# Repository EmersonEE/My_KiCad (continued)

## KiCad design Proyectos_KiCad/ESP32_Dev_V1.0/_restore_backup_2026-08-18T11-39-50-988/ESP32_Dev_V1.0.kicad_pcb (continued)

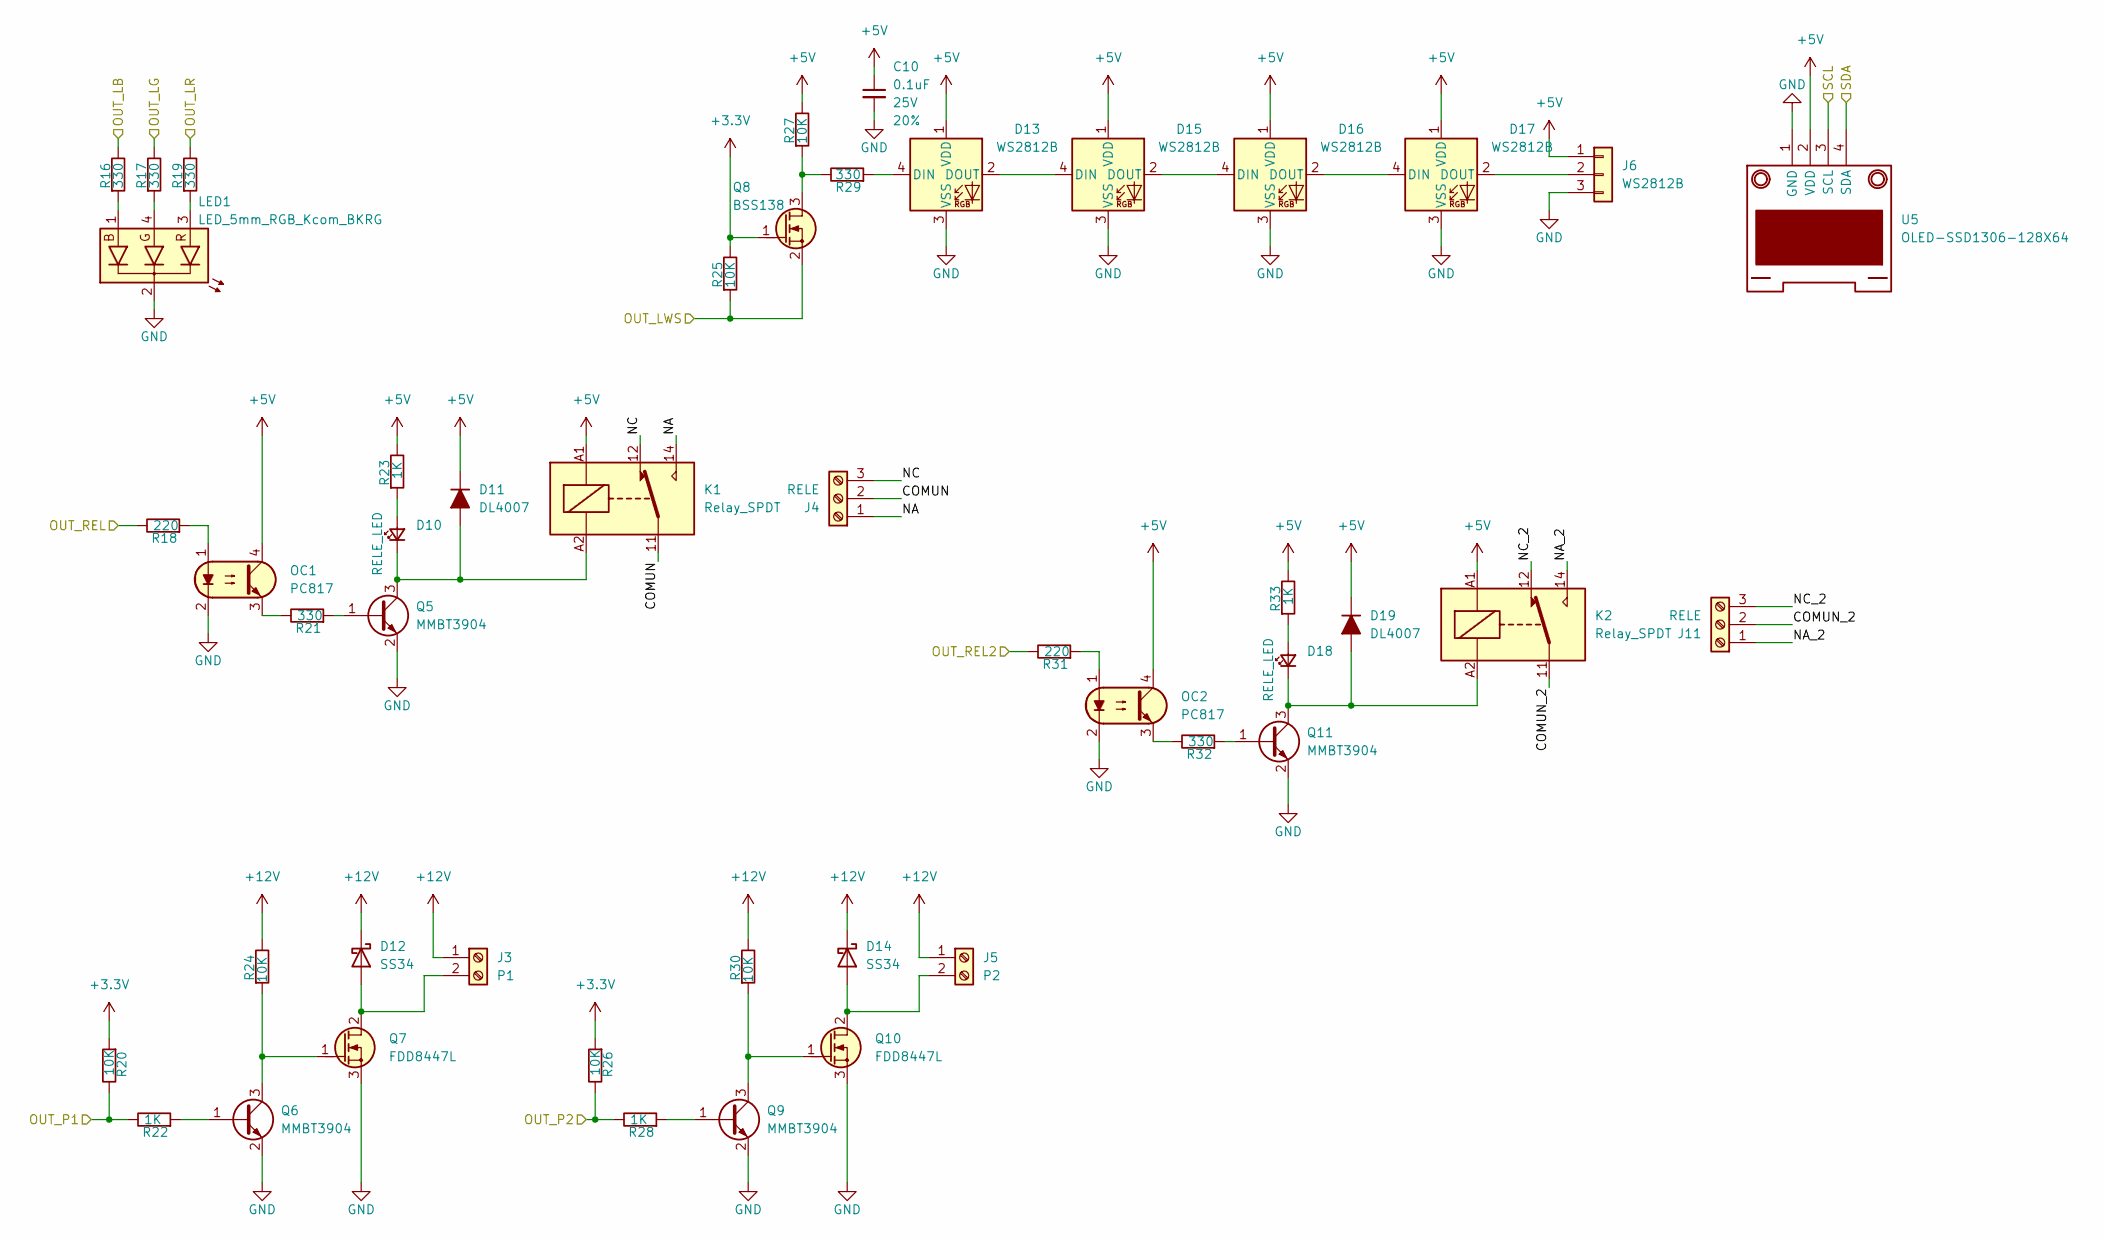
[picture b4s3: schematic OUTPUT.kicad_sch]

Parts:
C10: 0.1uF; C_0805_2012Metric; Voltage 25V; Tolerance 20%
D10, D18: RELE_LED; LED_0805_2012Metric
D11, D19: DL4007; D_SMA
D12, D14: SS34; D_SMA
D13, D15, D16, D17: WS2812B; LED_WS2812B_PLCC4_5.0x5.0mm_P3.2mm
J3: P1; TerminalBlock_Phoenix_MKDS-1,5-2-5.08_1x02_P5.08mm_Horizont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
J4, J11: RELE; TerminalBlock_Phoenix_MKDS-1,5-3-5.08_1x03_P5.08mm_Horizont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
J5: P2; TerminalBlock_Phoenix_MKDS-1,5-2-5.08_1x02_P5.08mm_Horizont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
J6: WS2812B; Molex_KK-254_AE-6410-03A_1x03_P2.54mm_Vertical
K1, K2: Relay_SPDT; Relay_SPDT_Finder_36.11
LED1: LED_5mm_RGB_Kcom_BKRG; LED_D5.0mm-4_RGB_Wide_Pins
OC1, OC2: PC817; DIP-4_W7.62mm_LongPads
Q5, Q6, Q9, Q11: MMBT3904; SOT-23
Q7, Q10: FDD8447L; TO-252-2
Q8: BSS138; SOT-23
R16, R17, R19, R21, R29, R32: 330; R_0805_2012Metric
R18, R31: 220; R_0805_2012Metric
R20, R24, R25, R26, R27, R30: 10K; R_0805_2012Metric
R22, R23, R28, R33: 1K; R_0805_2012Metric
U5: OLED-SSD1306-128X64; PinSocket_1x04_P2.54mm_Vertical

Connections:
+3.3V: Q8.1 (G), R20.1, R25.2, R26.1; also elsewhere on the board
+5V: C10.1, D11.1 (K), D13.1 (VDD), D15.1 (VDD), D16.1 (VDD), D17.1 (VDD), D19.1 (K), J6.1, K1.A1, K2.A1, OC1.4, OC2.4, R23.2, R27.2, R33.2, U5.2 (VDD); also elsewhere on the board
+12V: D12.1 (K), D14.1 (K), J3.1, J5.1, R24.2, R30.2; also elsewhere on the board
/Microcontroller/OUT_LB: R16.2; also elsewhere on the board
/Microcontroller/OUT_LG: R17.2; also elsewhere on the board
/Microcontroller/OUT_LR: R19.2; also elsewhere on the board
/Microcontroller/OUT_LWS: Q8.2 (S), R25.1; also elsewhere on the board
/Microcontroller/OUT_P1: R20.2, R22.2; also elsewhere on the board
/Microcontroller/OUT_P2: R26.2, R28.2; also elsewhere on the board
/Microcontroller/OUT_REL: R18.2; also elsewhere on the board
/Microcontroller/OUT_REL2: R31.2; also elsewhere on the board
/Microcontroller/SCL: U5.3 (SCL); also elsewhere on the board
/Microcontroller/SDA: U5.4 (SDA); also elsewhere on the board
/OUTPUT/COMUN: J4.2, K1.11
/OUTPUT/COMUN_2: J11.2, K2.11
/OUTPUT/NA: J4.1, K1.14
/OUTPUT/NA_2: J11.1, K2.14
/OUTPUT/NC: J4.3, K1.12
/OUTPUT/NC_2: J11.3, K2.12
GND: C10.2, D13.3 (VSS), D15.3 (VSS), D16.3 (VSS), D17.3 (VSS), J6.3, LED1.2 (A), OC1.2, OC2.2, Q5.2 (E), Q6.2 (E), Q7.3 (S), Q9.2 (E), Q10.3 (S), Q11.2 (E), U5.1 (GND); also elsewhere on the board
unnamed: D10.2 (A), R23.1
unnamed: D10.1 (K), D11.2 (A), K1.A2, Q5.3 (C)
unnamed: D12.2 (A), J3.2, Q7.2 (D)
unnamed: D13.4 (DIN), R29.1
unnamed: D13.2 (DOUT), D15.4 (DIN)
unnamed: D14.2 (A), J5.2, Q10.2 (D)
unnamed: D15.2 (DOUT), D16.4 (DIN)
unnamed: D16.2 (DOUT), D17.4 (DIN)
unnamed: D17.2 (DOUT), J6.2
unnamed: D18.2 (A), R33.1
unnamed: D18.1 (K), D19.2 (A), K2.A2, Q11.3 (C)
unnamed: LED1.1 (B), R16.1
unnamed: LED1.4 (G), R17.1
unnamed: LED1.3 (R), R19.1
unnamed: OC1.1, R18.1
unnamed: OC1.3, R21.2
unnamed: OC2.1, R31.1
unnamed: OC2.3, R32.2
unnamed: Q5.1 (B), R21.1
unnamed: Q6.1 (B), R22.1
unnamed: Q6.3 (C), Q7.1 (G), R24.1
unnamed: Q8.3 (D), R27.1, R29.2
unnamed: Q9.1 (B), R28.1
unnamed: Q9.3 (C), Q10.1 (G), R30.1
unnamed: Q11.1 (B), R32.1

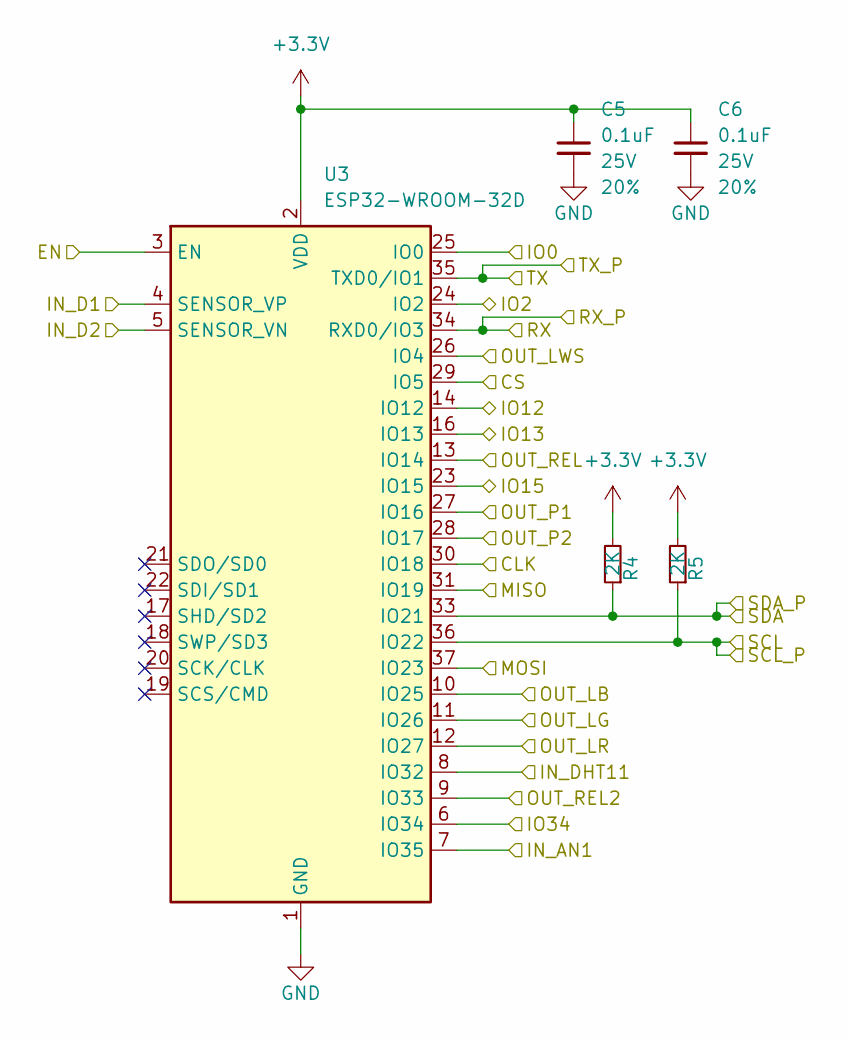
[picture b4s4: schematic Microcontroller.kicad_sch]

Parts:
C5, C6: 0.1uF; C_0805_2012Metric; Voltage 25V; Tolerance 20%
R4, R5: 2K; R_0805_2012Metric
U3: ESP32-WROOM-32D

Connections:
+3.3V: C5.1, C6.1, R4.2, R5.2, U3.2 (VDD); also elsewhere on the board
/INPUTS/IN_AN1: U3.7 (IO35); also elsewhere on the board
/INPUTS/IN_D1: U3.4 (SENSOR_VP); also elsewhere on the board
/INPUTS/IN_D2: U3.5 (SENSOR_VN); also elsewhere on the board
/INPUTS/IN_DHT11: U3.8 (IO32); also elsewhere on the board
/Microcontroller/CLK: U3.30 (IO18); also elsewhere on the board
/Microcontroller/CS: U3.29 (IO5); also elsewhere on the board
/Microcontroller/IO2: U3.24 (IO2); also elsewhere on the board
/Microcontroller/IO12: U3.14 (IO12); also elsewhere on the board
/Microcontroller/IO13: U3.16 (IO13); also elsewhere on the board
/Microcontroller/IO15: U3.23 (IO15); also elsewhere on the board
/Microcontroller/IO34: U3.6 (IO34); also elsewhere on the board
/Microcontroller/MISO: U3.31 (IO19); also elsewhere on the board
/Microcontroller/MOSI: U3.37 (IO23); also elsewhere on the board
/Microcontroller/OUT_LB: U3.10 (IO25); also elsewhere on the board
/Microcontroller/OUT_LG: U3.11 (IO26); also elsewhere on the board
/Microcontroller/OUT_LR: U3.12 (IO27); also elsewhere on the board
/Microcontroller/OUT_LWS: U3.26 (IO4); also elsewhere on the board
/Microcontroller/OUT_P1: U3.27 (IO16); also elsewhere on the board
/Microcontroller/OUT_P2: U3.28 (IO17); also elsewhere on the board
/Microcontroller/OUT_REL: U3.13 (IO14); also elsewhere on the board
/Microcontroller/OUT_REL2: U3.9 (IO33); also elsewhere on the board
/Microcontroller/RX: U3.34 (RXD0/IO3); also elsewhere on the board
/Microcontroller/SCL: R5.1, U3.36 (IO22); also elsewhere on the board
/Microcontroller/SDA: R4.1, U3.33 (IO21); also elsewhere on the board
/Microcontroller/TX: U3.35 (TXD0/IO1); also elsewhere on the board
/USB/EN: U3.3 (EN); also elsewhere on the board
/USB/IO0: U3.25 (IO0); also elsewhere on the board
GND: C5.2, C6.2, U3.1 (GND), U3.15 (GND), U3.38 (GND), U3.39 (GND); also elsewhere on the board

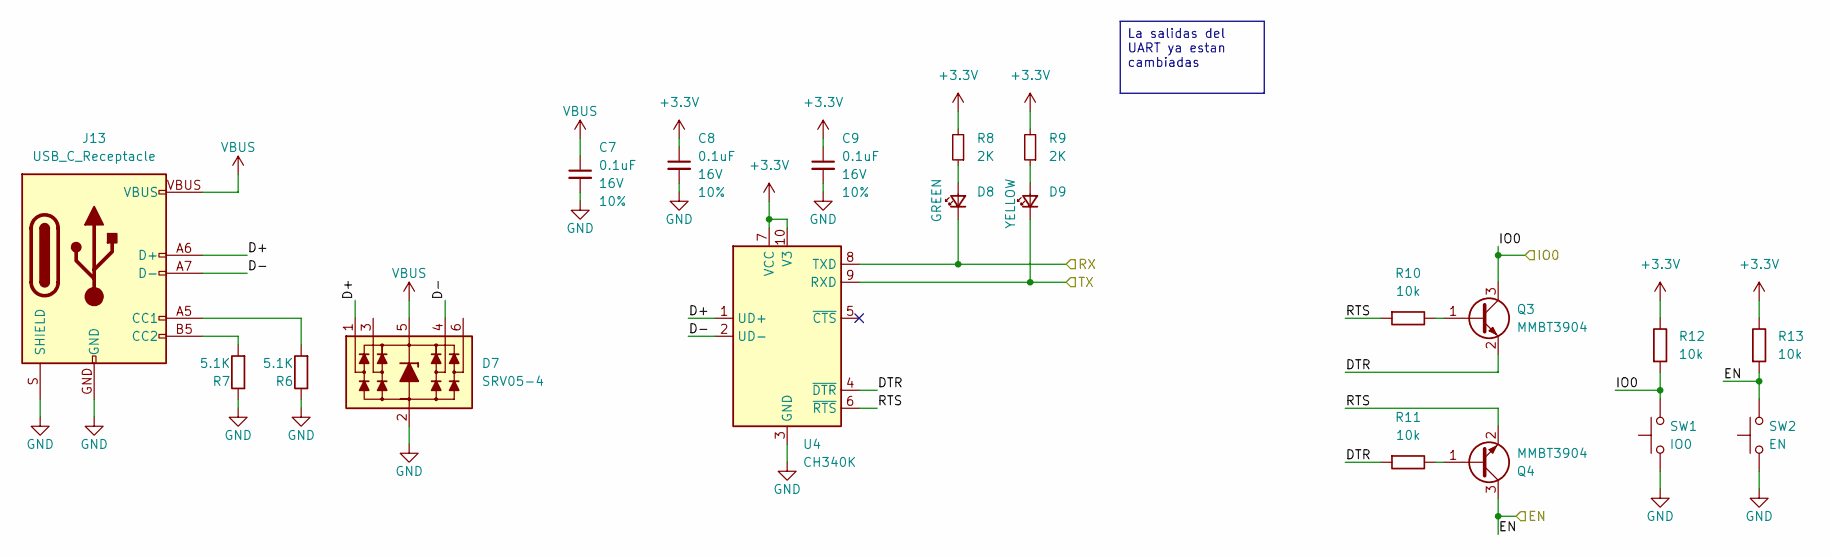
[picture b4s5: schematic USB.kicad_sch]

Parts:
C7, C8, C9: 0.1uF; C_0805_2012Metric; Voltage 16V; Tolerance 10%
D7: SRV05-4; SOT-23-6
D8: GREEN; LED_0805_2012Metric
D9: YELLOW; LED_0805_2012Metric
J13: USB_C_Receptacle; USB-C_16
Q3, Q4: MMBT3904; SOT-23
R6, R7: 5.1K; R_0805_2012Metric
R8, R9: 2K; R_0805_2012Metric
R10, R11, R12, R13: 10k; R_0805_2012Metric
SW1: IO0; Push_SMD_6x3.5mm; Mfg Part# 8-004 SMD Button 8x3.6mm Height=2.5mm
SW2: EN; Push_SMD_6x3.5mm; Mfg Part# 8-004 SMD Button 8x3.6mm Height=2.5mm
U4: CH340K; SSOP-10-1EP_3.9x4.9mm_P1mm_EP2.1x3.3mm

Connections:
+3.3V: C8.1, C9.1, R8.2, R9.2, R12.2, R13.2, U4.7 (VCC), U4.10 (V3); also elsewhere on the board
/Microcontroller/RX: D8.1 (K), U4.8 (TXD); also elsewhere on the board
/Microcontroller/TX: D9.1 (K), U4.9 (RXD); also elsewhere on the board
/USB/D+: D7.1 (L1), J13.A6 (D+), J13.B6 (D+), U4.1 (UD+)
/USB/D-: D7.4 (L3), J13.A7 (D-), J13.B7 (D-), U4.2 (UD-)
/USB/DTR: Q3.2 (E), R11.1, U4.4 (~DTR)
/USB/EN: Q4.3 (C), R13.1, SW2.2; also elsewhere on the board
/USB/IO0: Q3.3 (C), R12.1, SW1.2; also elsewhere on the board
/USB/RTS: Q4.2 (E), R10.1, U4.6 (~RTS)
GND: C7.2, C8.2, C9.2, D7.2 (VN), J13.GND, J13.S (SHIELD), R6.2, R7.2, SW1.1, SW2.1, U4.3 (GND), U4.11 (GND); also elsewhere on the board
unnamed: D8.2 (A), R8.1
unnamed: D9.2 (A), R9.1
unnamed: J13.A5 (CC1), R6.1
unnamed: J13.B5 (CC2), R7.1
unnamed: Q3.1 (B), R10.2
unnamed: Q4.1 (B), R11.2
VBUS: C7.1, D7.5 (VP), J13.VBUS; also elsewhere on the board

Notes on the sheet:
La salidas del UART ya estan cambiadas

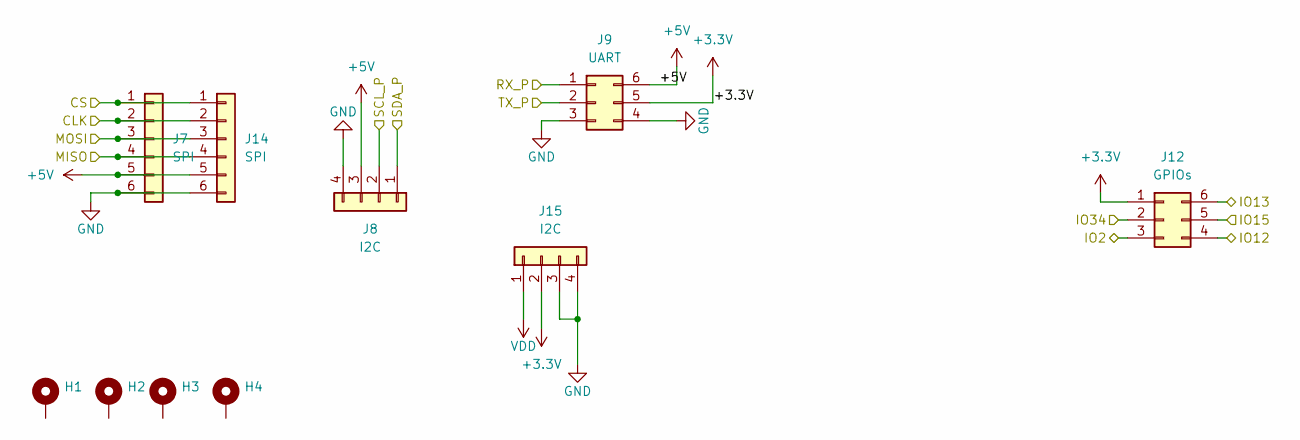
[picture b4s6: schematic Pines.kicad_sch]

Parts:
H1, H2, H3, H4: MountingHole_3.2mm_M3_Pad_Via
J7, J14: SPI; PinHeader_1x06_P2.54mm_Vertical
J8, J15: I2C; PinHeader_1x04_P2.54mm_Vertical
J9: UART; PinHeader_2x03_P2.54mm_Vertical
J12: GPIOs; PinHeader_2x03_P2.54mm_Vertical

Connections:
+3.3V: J9.5, J12.1, J15.2; also elsewhere on the board
+5V: J7.5, J8.3, J9.6, J14.5; also elsewhere on the board
/Microcontroller/CLK: J7.2, J14.2; also elsewhere on the board
/Microcontroller/CS: J7.1, J14.1; also elsewhere on the board
/Microcontroller/IO2: J12.6; also elsewhere on the board
/Microcontroller/IO12: J12.2; also elsewhere on the board
/Microcontroller/IO13: J12.5; also elsewhere on the board
/Microcontroller/IO15: J12.3; also elsewhere on the board
/Microcontroller/IO34: J12.4; also elsewhere on the board
/Microcontroller/MISO: J7.4, J14.4; also elsewhere on the board
/Microcontroller/MOSI: J7.3, J14.3; also elsewhere on the board
/Microcontroller/RX: J9.1; also elsewhere on the board
/Microcontroller/SCL: J8.2; also elsewhere on the board
/Microcontroller/SDA: J8.1; also elsewhere on the board
/Microcontroller/TX: J9.2; also elsewhere on the board
GND: J7.6, J8.4, J9.3, J9.4, J14.6, J15.3, J15.4; also elsewhere on the board
VDD: J15.1; also elsewhere on the board

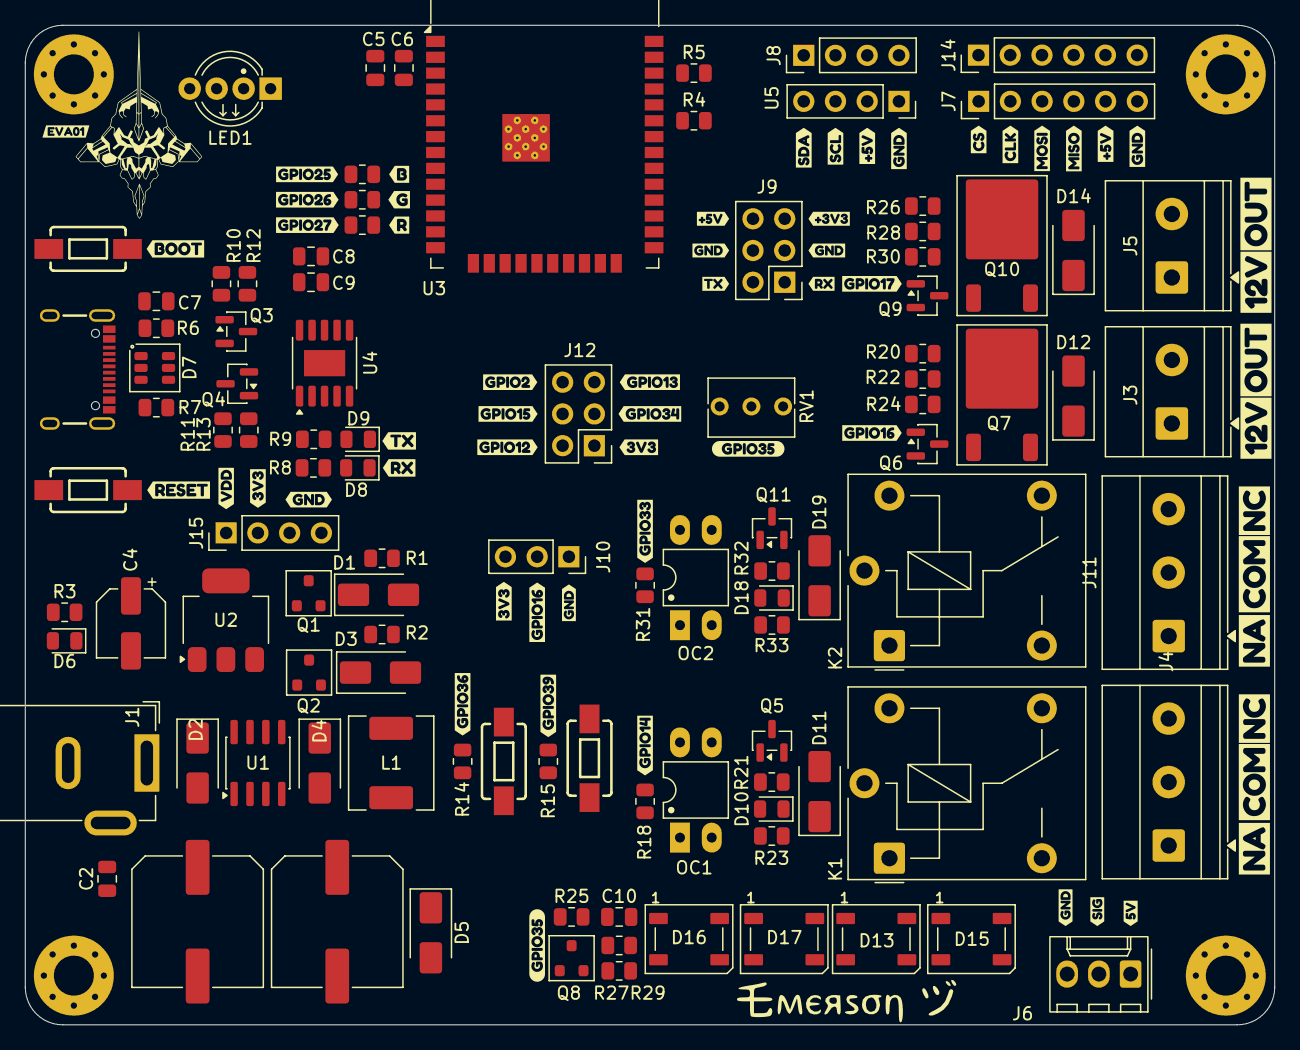
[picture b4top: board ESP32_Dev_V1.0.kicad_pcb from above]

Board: 4 copper layers, 100.0 x 80.0 mm, 167 parts (0 on the bottom side), 80 nets.

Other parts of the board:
kibuzzard-6A727B20: G***; kibuzzard-6A727B20
kibuzzard-6A727BCE: G***; kibuzzard-6A727BCE
kibuzzard-6A727C1E: G***; kibuzzard-6A727C1E
kibuzzard-6A727C6D: G***; kibuzzard-6A727C6D
kibuzzard-6A727C11: G***; kibuzzard-6A727C11
kibuzzard-6A727C18: G***; kibuzzard-6A727C18
kibuzzard-6A727C24, kibuzzard-6A727C24#2: G***; kibuzzard-6A727C24
kibuzzard-6A727C29, kibuzzard-6A727C29#2: G***; kibuzzard-6A727C29
kibuzzard-6A727C74: G***; kibuzzard-6A727C74
kibuzzard-6A727DDB: G***; kibuzzard-6A727DDB
kibuzzard-6A727DF1: G***; kibuzzard-6A727DF1
kibuzzard-6A727ECC, kibuzzard-6A727ECC#2: G***; kibuzzard-6A727ECC
kibuzzard-6A727ED5, kibuzzard-6A727ED5#2: G***; kibuzzard-6A727ED5
kibuzzard-6A7277D2: G***; kibuzzard-6A7277D2
kibuzzard-6A7277EF: G***; kibuzzard-6A7277EF
kibuzzard-6A7277F6: G***; kibuzzard-6A7277F6
kibuzzard-6A7278A5: G***; kibuzzard-6A7278A5
kibuzzard-6A7278D2: G***; kibuzzard-6A7278D2
kibuzzard-6A7278D7: G***; kibuzzard-6A7278D7
kibuzzard-6A7278E0, kibuzzard-6A7278E0#2: G***; kibuzzard-6A7278E0
kibuzzard-6A7278F5: G***; kibuzzard-6A7278F5
kibuzzard-6A7279A2, kibuzzard-6A7279A2#2: G***; kibuzzard-6A7279A2
kibuzzard-6A7280AD: G***; kibuzzard-6A7280AD
kibuzzard-6A7281CE: G***; kibuzzard-6A7281CE
kibuzzard-6A7281DF: G***; kibuzzard-6A7281DF
kibuzzard-6A7281E6: G***; kibuzzard-6A7281E6
kibuzzard-6A7283B1: G***; kibuzzard-6A7283B1
kibuzzard-6A72633A, kibuzzard-6A72633A#2: G***; kibuzzard-6A72633A
kibuzzard-6A72787D: G***; kibuzzard-6A72787D
kibuzzard-6A72789E: G***; kibuzzard-6A72789E
kibuzzard-6A72791D, kibuzzard-6A72791D#2: G***; kibuzzard-6A72791D
kibuzzard-6A72793C: G***; kibuzzard-6A72793C
kibuzzard-6A72838F: G***; kibuzzard-6A72838F
kibuzzard-6A726309, kibuzzard-6A726309#2: G***; kibuzzard-6A726309
kibuzzard-6A726341, kibuzzard-6A726341#2: G***; kibuzzard-6A726341
kibuzzard-6A727472: G***; kibuzzard-6A727472
kibuzzard-6A727479, kibuzzard-6A727479#2: G***; kibuzzard-6A727479
kibuzzard-6A727480: G***; kibuzzard-6A727480
kibuzzard-6A727489: G***; kibuzzard-6A727489
kibuzzard-6A727492: G***; kibuzzard-6A727492
kibuzzard-6A727498: G***; kibuzzard-6A727498
kibuzzard-6A727875: G***; kibuzzard-6A727875
kibuzzard-6A727895: G***; kibuzzard-6A727895
kibuzzard-6A727942: G***; kibuzzard-6A727942
kibuzzard-6A727946: G***; kibuzzard-6A727946
kibuzzard-6A728113: G***; kibuzzard-6A728113
kibuzzard-6A728159: G***; kibuzzard-6A728159
kibuzzard-6A728349: G***; kibuzzard-6A728349
kibuzzard-6A728389: G***; kibuzzard-6A728389

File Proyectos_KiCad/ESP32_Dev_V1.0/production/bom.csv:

Designator,Footprint,Quantity,Value,LCSC Part #
C1,Electrolytic_10.3x10.3mm,1,470uF,
"C10, C2, C5, C6, C7, C8, C9",0805,7,0.1uF,
C3,Electrolytic_10.3x10.3mm,1,220uF,
C4,CP_Elec_5x5.3,1,10uF,
"D1, D12, D14, D2, D3, D4, D5",D_SMA,7,SS34,
"D10, D18",0805,2,RELE_LED,
"D11, D19",D_SMA,2,DL4007,
"D13, D15, D16, D17",LED_WS2812B_PLCC4_5.0x5.0mm_P3.2mm,4,WS2812B,
D6,0805,1,LED,
D7,SOT-23-6,1,SRV05-4,
D8,0805,1,GREEN,
D9,0805,1,YELLOW,
J1,BarrelJack_GCT_DCJ200-10-A_Horizontal,1,Barrel_Jack_Switch,
"J11, J4","TerminalBlock_Phoenix_MKDS-1,5-3-5.08_1x03_P5.08mm_Horizontal",2,RELE,
J12,PinHeader_2x03_P2.54mm_Vertical,1,GPIOs,
J13,USB-C_16,1,USB_C_Receptacle,
"J14, J7",PinHeader_1x06_P2.54mm_Vertical,2,SPI,
"J15, J8",PinHeader_1x04_P2.54mm_Vertical,2,I2C,
J3,"TerminalBlock_Phoenix_MKDS-1,5-2-5.08_1x02_P5.08mm_Horizontal",1,P1,
J5,"TerminalBlock_Phoenix_MKDS-1,5-2-5.08_1x02_P5.08mm_Horizontal",1,P2,
J6,Molex_KK-254_AE-6410-03A_1x03_P2.54mm_Vertical,1,WS2812B,
J9,PinHeader_2x03_P2.54mm_Vertical,1,UART,
"K1, K2",Relay_SPDT_Finder_36.11,2,Relay_SPDT,
L1,L_AVX_LMLP07A7,1,68uH,
LED1,LED_D5.0mm-4_RGB_Wide_Pins,1,LED_5mm_RGB_Kcom_BKRG,
"OC1, OC2",DIP-4_W7.62mm_LongPads,2,PC817,
"Q1, Q2",SOT-23,2,DMP3056L,
"Q10, Q7",TO-252-2,2,FDD8447L,
"Q11, Q3, Q4, Q5, Q6, Q9",SOT-23,6,MMBT3904,
Q8,SOT-23,1,BSS138,
"R1, R10, R11, R12, R13, R14, R15, R2, R20, R24, R25, R26, R27, R30",0805,14,10k,
"R16, R17, R19, R21, R29, R32",0805,6,330,
"R18, R31",0805,2,220,
"R22, R23, R28, R3, R33",0805,5,1K,
"R4, R5, R8, R9",0805,4,2K,
"R6, R7",0805,2,5.1K,
RV1,Potentiometer_Bourns_3266Y_Vertical,1,IN3,
SW1,Push_SMD_6x3.5mm,1,IO0,
SW2,Push_SMD_6x3.5mm,1,EN,
SW3,Push_SMD_6x3.5mm,1,IN1,
SW4,Push_SMD_6x3.5mm,1,IN2,
U1,SOIC-8_3.9x4.9mm_P1.27mm,1,XL1509-5.0,
U2,SOT-223-3_TabPin2,1,AMS1117-3.3,
U3,ESP32-WROOM-32D,1,ESP32-WROOM-32D,
U4,SSOP-10-1EP_3.9x4.9mm_P1mm_EP2.1x3.3mm,1,CH340K,
U5,PinSocket_1x04_P2.54mm_Vertical,1,OLED-SSD1306-128X64,

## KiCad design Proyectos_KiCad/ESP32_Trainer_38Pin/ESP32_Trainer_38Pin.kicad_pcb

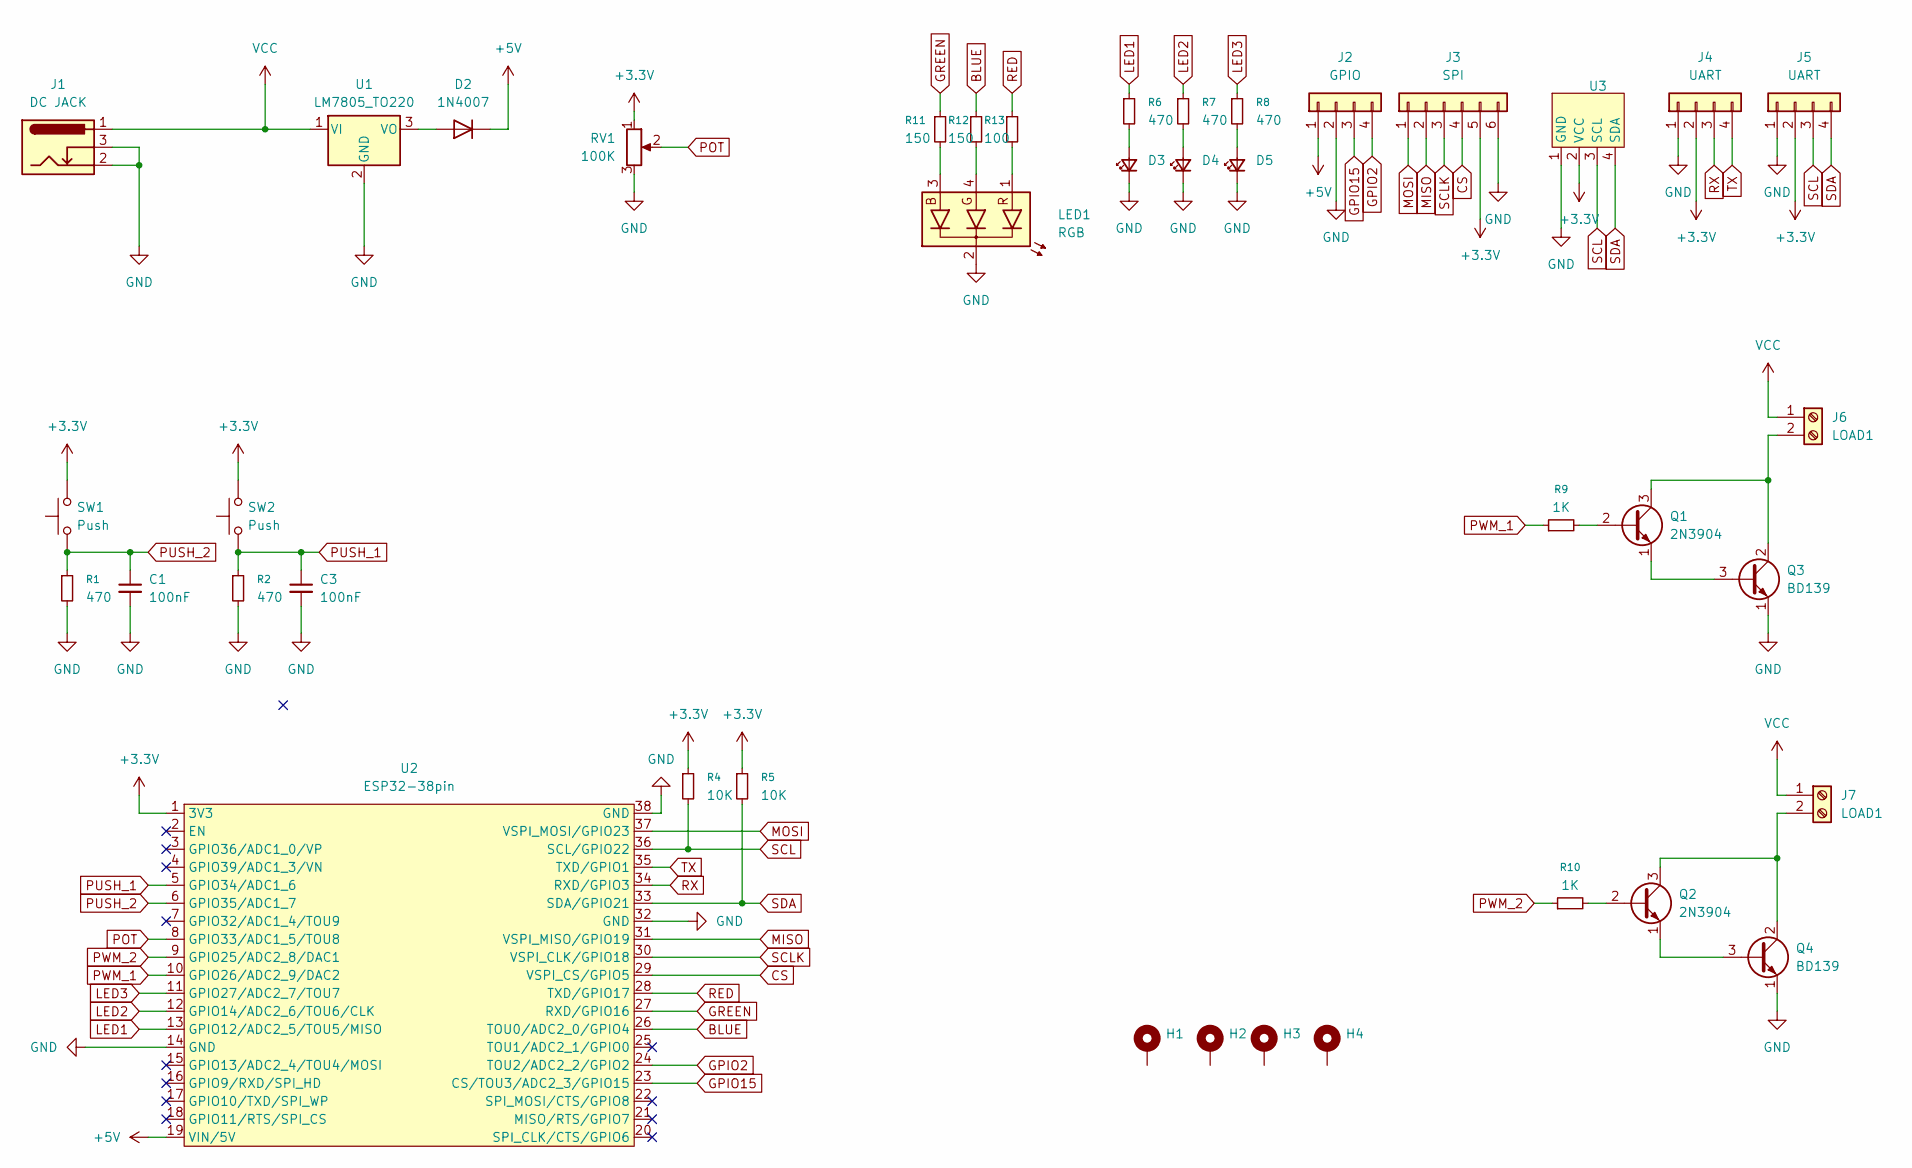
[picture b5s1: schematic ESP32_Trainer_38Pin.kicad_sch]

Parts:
C1, C3: 100nF; C_Disc_D3.8mm_W2.6mm_P2.50mm
D2: 1N4007; D_DO-41_SOD81_P10.16mm_Horizontal
D3, D4, D5: LED_D3.0mm
H1, H2, H3, H4: MountingHole_3.2mm_M3_Pad_Via
J1: DC JACK; BarrelJack_Horizontal
J2: GPIO; PinHeader_1x04_P2.54mm_Vertical
J3: SPI; PinHeader_1x06_P2.54mm_Vertical
J4, J5: UART; PinHeader_1x04_P2.54mm_Vertical
J6, J7: LOAD1; TerminalBlock_Phoenix_MKDS-1,5-2-5.08_1x02_P5.08mm_Horizont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
LED1: RGB; LED_D5.0mm-4_RGB_Wide_Pins
Q1, Q2: 2N3904; SOT-23_BigPads
Q3, Q4: BD139; TO-126-3_Vertical
R1, R2: 470; R_1206_3216Metric_Pad1.30x1.75mm_HandSolder
R4, R5: 10K
R6, R7, R8: 470; R_1206_3216Metric_Pad1.42x1.75mm_HandSolder
R9, R10: 1K; R_1206_3216Metric_Pad1.42x1.75mm_HandSolder
R11, R12: 150; R_1206_3216Metric_Pad1.42x1.75mm_HandSolder
R13: 100; R_1206_3216Metric_Pad1.42x1.75mm_HandSolder
RV1: 100K; Potentiometer_Bourns_3266Y_Vertical
SW1, SW2: Push; SW_PUSH_6mm
U1: LM7805_TO220; TO-220-3_Horizontal_TabDown
U2: ESP32-38pin; ESP32_DevKit_38Pin
U3: SSD1306

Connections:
+3.3V: J3.5, J4.2, J5.2, R4.1, R5.1, RV1.1, SW1.2, SW2.2, U2.1 (3V3), U3.2 (VCC)
+5V: D2.1 (K), J2.1, U2.19 (VIN/5V)
BLUE: R12.1, U2.26 (TOU0/ADC2_0/GPIO4)
CS: J3.4, U2.29 (VSPI_CS/GPIO5)
GND: C1.2, C3.2, D3.1 (K), D4.1 (K), D5.1 (K), J1.2, J1.3, J2.2, J3.6, J4.1, J5.1, LED1.2 (A), Q3.1 (E), Q4.1 (E), R1.2, R2.2, RV1.3, U1.2 (GND), U2.14 (GND), U2.32 (GND), U2.38 (GND), U3.1 (GND)
GPIO2: J2.4, U2.24 (TOU2/ADC2_2/GPIO2)
GPIO15: J2.3, U2.23 (CS/TOU3/ADC2_3/GPIO15)
GREEN: R11.1, U2.27 (RXD/GPIO16)
LED1: R6.1, U2.13 (GPIO12/ADC2_5/TOU5/MISO)
LED2: R7.1, U2.12 (GPIO14/ADC2_6/TOU6/CLK)
LED3: R8.1, U2.11 (GPIO27/ADC2_7/TOU7)
MISO: J3.2, U2.31 (VSPI_MISO/GPIO19)
MOSI: J3.1, U2.37 (VSPI_MOSI/GPIO23)
unnamed: D2.2 (A), U1.3 (VO)
unnamed: D3.2 (A), R6.2
unnamed: D4.2 (A), R7.2
unnamed: D5.2 (A), R8.2
unnamed: J6.2, Q1.3 (C), Q3.2 (C)
unnamed: J7.2, Q2.3 (C), Q4.2 (C)
unnamed: LED1.3 (B), R11.2
unnamed: LED1.4 (G), R12.2
unnamed: LED1.1 (R), R13.2
unnamed: Q1.2 (B), R9.2
unnamed: Q1.1 (E), Q3.3 (B)
unnamed: Q2.2 (B), R10.2
unnamed: Q2.1 (E), Q4.3 (B)
POT: RV1.2, U2.8 (GPIO33/ADC1_5/TOU8)
PUSH_1: C3.1, R2.1, SW2.1, U2.5 (GPIO34/ADC1_6)
PUSH_2: C1.1, R1.1, SW1.1, U2.6 (GPIO35/ADC1_7)
PWM_1: R9.1, U2.10 (GPIO26/ADC2_9/DAC2)
PWM_2: R10.1, U2.9 (GPIO25/ADC2_8/DAC1)
RED: R13.1, U2.28 (TXD/GPIO17)
RX: J4.3, U2.34 (RXD/GPIO3)
SCL: J5.3, R4.2, U2.36 (SCL/GPIO22), U3.3 (SCL)
SCLK: J3.3, U2.30 (VSPI_CLK/GPIO18)
SDA: J5.4, R5.2, U2.33 (SDA/GPIO21), U3.4 (SDA)
TX: J4.4, U2.35 (TXD/GPIO1)
VCC: J1.1, J6.1, J7.1, U1.1 (VI)

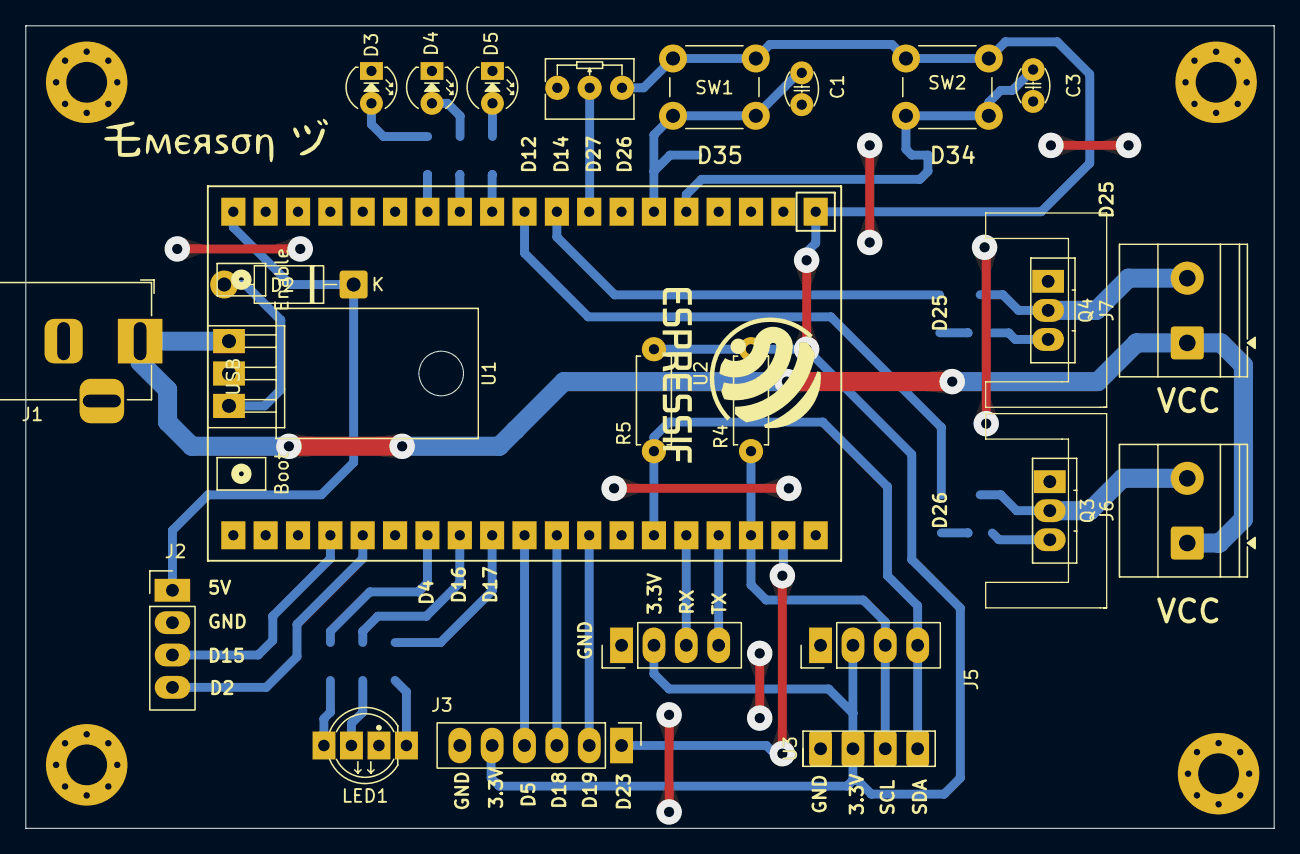
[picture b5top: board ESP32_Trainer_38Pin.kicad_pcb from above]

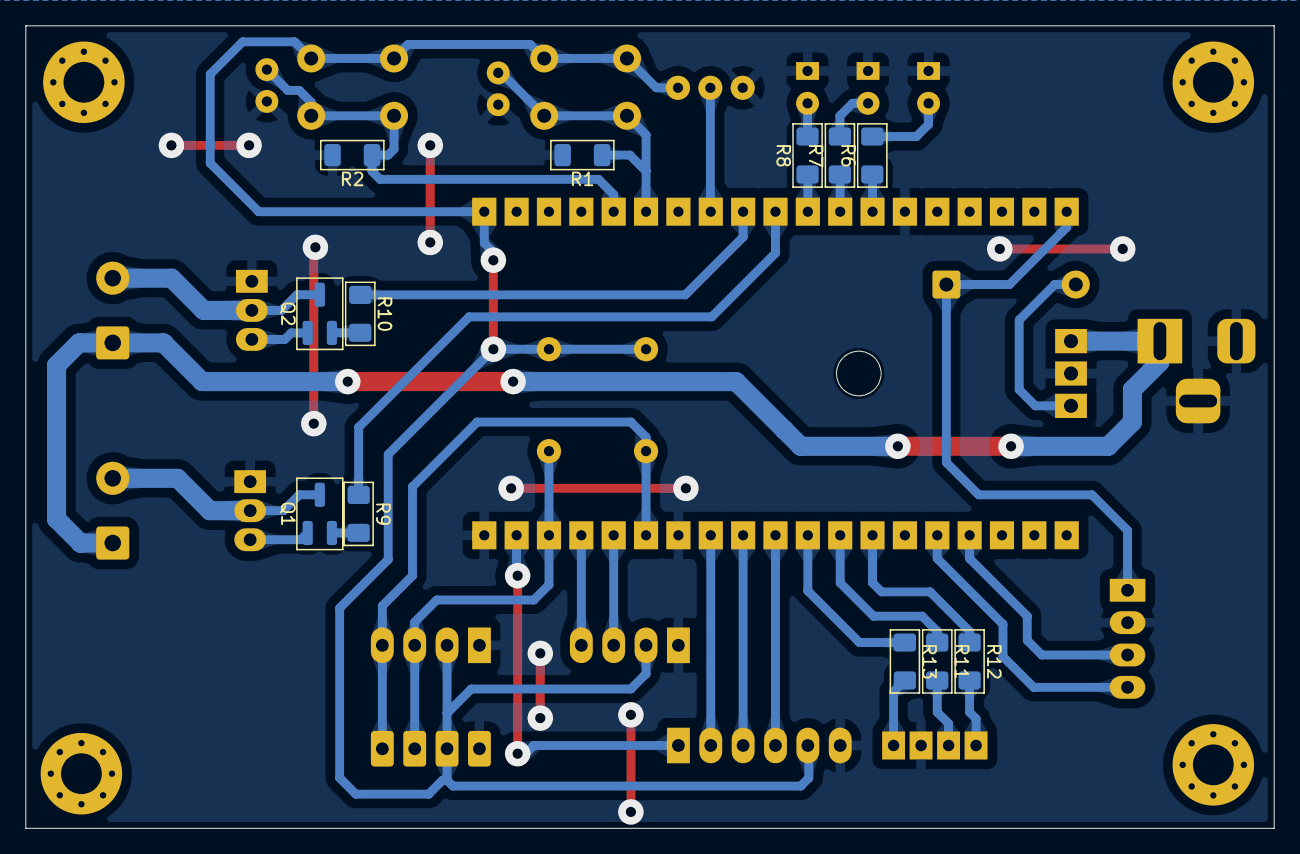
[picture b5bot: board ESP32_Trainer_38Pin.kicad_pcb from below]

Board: 2 copper layers, 98.0 x 63.0 mm, 40 parts (12 on the bottom side), 38 nets.

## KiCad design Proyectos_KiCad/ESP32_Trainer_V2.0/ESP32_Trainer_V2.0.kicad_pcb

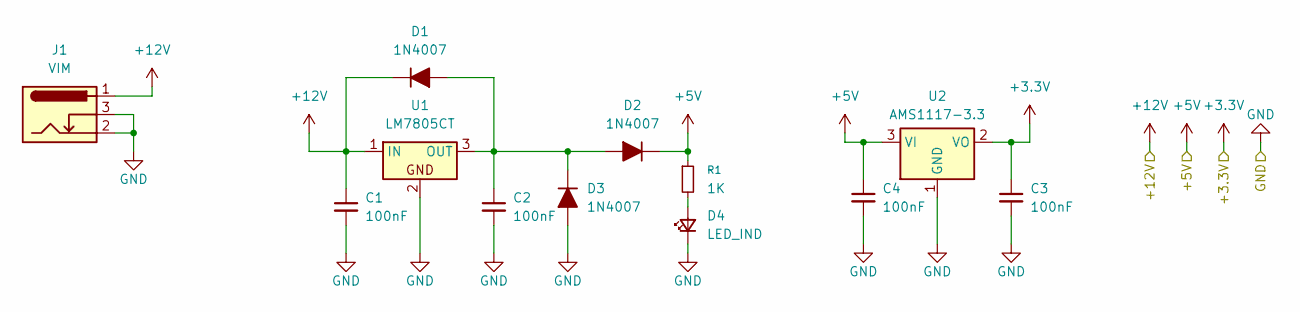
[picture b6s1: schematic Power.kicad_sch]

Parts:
C1, C2, C3, C4: 100nF; C_Disc_D4.3mm_W1.9mm_P5.00mm
D1, D2, D3: 1N4007; D_SMA
D4: LED_IND; LED_1206_3216Metric_Pad1.42x1.75mm
J1: VIM; BarrelJack_GCT_DCJ200-10-A_Horizontal
R1: 1K; R_0805_2012Metric_Pad1.15x1.40mm
U1: LM7805CT; TO-220-3_Vertical
U2: AMS1117-3.3; SOT-223-3_TabPin2

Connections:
+3.3V: C3.1, U2.2 (VO); also elsewhere on the board
+5V: C4.1, D2.1 (K), R1.1, U2.3 (VI); also elsewhere on the board
+12V: C1.1, D1.1 (K), J1.1, U1.1 (IN); also elsewhere on the board
GND: C1.2, C2.2, C3.2, C4.2, D3.2 (A), D4.1 (K), J1.2, J1.3, U1.2, U2.1 (GND); also elsewhere on the board
unnamed: C2.1, D1.2 (A), D2.2 (A), D3.1 (K), U1.3 (OUT)
unnamed: D4.2 (A), R1.2
